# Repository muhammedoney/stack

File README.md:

# Stack — FPV uçuş kontrol ve ESC kartları

**Stack**, FPV dronlar için bir uçuş kontrol kartı (FMU) ile 4’ü 1 arada ESC kartlarından oluşan, 30.5 × 30.5 mm montaj desenli bir yığındır. Tasarımlar cezeri reposundaki Altium çalışmalarından ve piyasadaki kartların tersine mühendisliğinden geliyor; KiCad 10’a taşınacak.

```
  RC alıcı / VTX / GPS ─► [ FMU: STM32F405, ICM-42688-P, BMP388, OSD, 9 V + 5 V BEC ] ─ 8 pin SM08B ─► [ ESC: 4 × EFM8BB21 + FD6288Q + 24 MOSFET ] ─► 4 motor
                                                    ▲                                                         │
                                                    └──────────────── CUR (akım), VBAT ◄──────────────────────┘
```

## Durum (2026-11-06)

| Kart | Kaynak | Şematik | PCB | Yazılım |
|---|---|---|---|---|
| [esc55a](boards/esc55a/README.md) — 4’ü 1 arada 55 A | Altium | 3 sayfa, 232 parça | 4 katman, 41 × 48 mm, yollu (bağlanmamış 0) | BLHeli_S/Bluejay düzeni doğrulanacak |
| esc65a — 4’ü 1 arada 65 A | drawio | yok (16 fotoğraf, 2 parça etiketi) | yok | — |
| [fmu](boards/fmu/README.md) — F405 uçuş kontrol | Altium | 1 sayfa, 143 parça | yok | Betaflight hedefi yazılacak |

Altium projeleri `boards/*/altium/` altında olduğu gibi duruyor; KiCad’e taşınmadı. Bulgular ve önerilen sıra: [docs/inceleme.md](docs/inceleme.md). Gereksinimler: 5" stack için 56 SYS, 90 DOG (53 Ü-öncesi) taslak; kapı 1 onayı bekleniyor ([docs/gereksinimler](docs/gereksinimler/README.md)).

## Belgeler

| Belge | İçerik |
|---|---|
| [İlk inceleme](docs/inceleme.md) | Kopyalanan dosyalar, mimari, hesaplar, bulgular (E1–E12, F1–F7), önerilen sıra |
| [Pazar analizi](docs/pazar-analizi.md) | Rakip stack’ler, özellikler, fiyatlar, hedef değer önerisi; ham veri `docs/pazar/rakipler.csv` |
| [BOM ve maliyet](docs/bom-maliyet.md) | 5" stack 5 / 100 / 1000 set maliyeti, muadiller, maliyet azaltma seçenekleri; ham BOM `boards/*/bom-maliyet.csv` |
| [Gereksinimler](docs/gereksinimler/README.md) | MUS/SYS/PRJ/DOG kaydı, açık sorular |
| `docs/esc55a.drawio`, `docs/esc65a.drawio` | ESC tersine mühendislik çizimleri |
| `docs/fmu-diatone-f405mk2.drawio`, `docs/fmu-geprc-f405-hd-v3.drawio` | FMU referans kart çizimleri; görseller `docs/reference/fmu/` |
| [CHANGELOG](CHANGELOG.md) | Değişiklik geçmişi |

## Klasörler

| Klasör | İçerik |
|---|---|
| `boards/` | Kart başına klasör: `altium/` (orijinal), `<ad>/` (KiCad projesi, taşımadan sonra), `README.md` |
| `lib/` | Ortak KiCad kütüphanesi (taşımada kurulacak); `lib/datasheet/` veri sayfaları |
| `firmware/` | ESC (Bluejay/BLHeli_S düzeni) ve FMU (Betaflight hedefi) yazılım dosyaları |
| `docs/` | Belgeler, drawio çizimleri, `docs/gereksinimler/`, `docs/reference/` |
| `test/` | Analiz betikleri, prosedürler, DOG sonuçları |
| `tools/` | Python betikleri: `altium_sch_dump.py` (SchDoc parça/ağ dökümü), `pcb_stat.py` (içe aktarılmış PCB özeti), `drawio_dump.py` |

## Geliştirici notları

Altium dosyalarını incelemek için (repo dışına, geçici dizine):

```bash
python3 -I tools/altium_sch_dump.py boards/esc55a/altium/main.SchDoc
```

```bash
LC_ALL=C.UTF-8 kicad-cli pcb import --format altium -o /tmp/esc55a.kicad_pcb boards/esc55a/altium/ESC_v0.PcbDoc
```

**Türkçe dil ayarı:** KiCad 10.0.7’nin Altium okuyucusu alan adlarını sistem diliyle büyük harfe çeviriyor; Türkçede “Location” “LOCATİON” olur. İçe aktarmayı `LC_ALL=C.UTF-8` ile yapın.

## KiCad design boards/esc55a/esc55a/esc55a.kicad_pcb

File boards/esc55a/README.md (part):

# esc55a — 4’ü 1 arada 55 A ESC

Dört kanallı BLHeli_S tipi ESC. Kanal başına EFM8BB21F16G (QFN20) → FD6288Q (QFN24) → 6 × ME7170 N-MOS (8DFN 5 × 6). JW5026 buck → 8.07 V (PVDD) → AMS1117 → 3V3. Yüksek taraf shunt 2 × 1 mΩ 2512 + INA199C1 → J0.1 CUR. FMU bağlantısı J0 SM08B-SRSS-TB. (Altium / İP-04 durumu; **şematik Rev B’de** sürücü JSM6288Q1, MOSFET BLP016N04LC-Q 40 V, akım ölçümü 0.1 mΩ 3920 + INA240A3; yüksek sıcaklık (2026-11-11): MCU EFM8BB21F16**I** 125 °C, X5R yok — bkz. [Rev B şematik](#rev-b-şematik-2026-11-10). PCB henüz Rev A.)

- Kaynak: Altium [`altium/esc55a.PrjPcb`](altium/esc55a.PrjPcb) — `main.SchDoc` (güç, MOSFET’ler, konnektör), `mcu2.SchDoc` (kanal 1–2), `mcu.SchDoc` (kanal 3–4), `ESC_v0.PcbDoc`. `FPV_Template.PcbDoc` projede yok (eski taslak); `escPan.PcbDoc` boş 100 × 100 mm panel (cezeri 2025-05-29: “maliyet avantajı olmadı”).
- PCB: 4 katman (dış ≈ 2 oz, iç 0.5 oz), 1.67 mm, 41.25 × 47.75 mm, montaj 30.5 × 30.5 mm M3. 224 ayak izi, 1730 yol parçası, 210 via, 34 bölge; bağlanmamış 0.
- KiCad (İP-04, 2026-11-10): PCB [`esc55a/esc55a.kicad_pcb`](esc55a/esc55a.kicad_pcb) `kicad-cli pcb import` ile alındı; Altium kuralları `.kicad_pro`’da (açıklık/iz 0.1 mm, via 0.45 / 0.2 mm, halka 0.1 mm, kenar 0.2 mm); ayak izleri `lib/{RLC,MOS,IC,CONN}.pretty` (`tools/altium_libs.py`); dış hattaki 4 sıfıra yakın parça silindi (`tools/outline_fix.py`). Proje klasörü `esc55a/`: `esc55a.kicad_pcb`, `.kicad_pro` (kurallar + şematik sayfaları), `.kicad_prl`, `fp-lib-table`, `sym-lib-table`, şematik (aşağıda).

## Şematik (İP-04, 2026-11-10)

Hiyerarşik: kök [`esc55a/esc55a.kicad_sch`](esc55a/esc55a.kicad_sch) → 3 alt sayfa.

| Sayfa | Dosya | Altium kaynağı | İçerik |
|---|---|---|---|
| main (s. 2) | `main.kicad_sch` | `main.SchDoc` | Güç (JW5026, AMS1117, INA199, shunt), 24 × ME7170, J0, pedler |
| mcu2 (s. 3) | `mcu2.kicad_sch` | `mcu2.SchDoc` | Kanal 1–2: U11/U21 EFM8BB21, U12/U22 FD6288Q |
| mcu (s. 4) | `mcu.kicad_sch` | `mcu.SchDoc` | Kanal 3–4: U31/U41 EFM8BB21, U32/U42 FD6288Q |

Taşıma adımları (tekrar için):

1. `LC_ALL=C.UTF-8 LANG=C.UTF-8 kicad` → *File → Import Non-KiCad Project → Altium Project* → `altium/esc55a.PrjPcb`, hedef boş bir klasör (ör. `.tmp_imp/out/`); PCB sorusuna “No” (PCB ayrı alındı). Türkçe dil ayarında okuyucu `Location` → `LOCATİON` yapıp çöker; dil ayarı zorunlu. KiCad 10 üç sayfayı üç üst düzey sayfa olarak yazar, ağ etiketlerini yerel yapar.
2. `python3 tools/esc55a_sch.py .tmp_imp/out` — kök + alt sayfa hiyerarşisi; birden çok sayfada geçen 41 ağ etiketi global etiket (Altium projesinde port/sayfa girişi yok → etiketler global); `R?` → R99–R106, `#PWR?` numaralandı; 29 NC işareti, 16 PWR_FLAG; `.kicad_pro` sayfa listesi.
3. `python3 tools/altium_libs.py` — semboller `lib/{RLC,IC,MOS,CONN,stack}.kicad_sym`, Footprint alanları PCB’den.

| Kontrol | Sonuç |
|---|---|
| Netlist ↔ PCB (pin → ağ, 707 ortak pin) | Ağ bölünmesi/birleşmesi 0; yalnız isimsiz ağların adı farklı (`Net-(C00-1)` ↔ `NetC00_P$1`) |
| ERC (`kicad-cli sch erc`) | 0 hata, 8 uyarı: 4 sarkan 2.54 mm tel ucu (CK1–CK4 pedi, Altium artığı, elektriksel etkisi yok); 2 çoklu ağ adı (PVDD etiketi = +8V güç portu; PCB’de ağ adı PVDD); 2 sembol–kütüphane farkı (C00, C04: dikdörtgen köşe sırası, yalnız çizim) |
| Referanslar | Benzersiz. `M1aH`, `P1a`, `BAT`, `gnd`, `3v`… Altium adları PCB ile eşleşsin diye korundu (rakamla bitmediği için KiCad “annotation” uyarısı verir; **Annotate çalıştırılmamalı**) |

Şematik ↔ PCB farkları (Altium’dan gelen, değiştirilmedi):

| Konu | Şematik | PCB |
|---|---|---|
| R99–R106 (eski `R?`): kanal başına 3 k → +VD, 1 k → GND, Ux1 pin 1’e (bölücü) | Var (Rev B: DNP, kartta yok) | **Yok** (224 ayak izi); Ux1 pin 1 boşta |
| J0 `GND` pini (sembol) | Pin adı `GND`, boşta (NC) | Ayak izinde `GND` pedi yok (P1/P2 montaj pedleri ağsız) |
| R99–R106 değer adı | `RES0402_3k_????` / `RES0402_1k_????` (Altium’da da bozuk karakter) | — |

## Rev B şematik (2026-11-10)

Kaynak: [`docs/rapor/guc-ip03.md`](../../docs/rapor/guc-ip03.md) önerileri; parça kodları `bom-maliyet.csv` / `bom-revb.csv`. Betik: `python3 tools/esc55a_revb.py` (idempotent: ikinci çalıştırma dosyaları değiştirmez; yeni UUID’ler sabit adlardan). Yardımcı: `tools/sch_edit.py` (fiber’den kopya, belirlenimci UUID eklendi). **PCB değiştirilmedi** (aşağıda senkron notu).

| # | Bulgu / SYS | Değişiklik | Referanslar |
|---|---|---|---|
| 1 | G1 · SYS-014, 010 | ME7170 30 V → **BLP016N04LC-Q** 40 V 1.6 mΩ (C49328363); ALT **NTMFS5C430NLT1G** (C194661). Ayak izi aynı `MOS:8DFN4.9X5.8` (DFN5×6, 1-3 S / 4 G / 5-8 D) | M1aH…M4cL (24) |
| 2 | G3 · SYS-016 | FD6288Q → **JSM6288Q1** (C52196409, UVLO 4.5 V); ALT FD6288Q (C328453). Pin/ayak izi aynı | U12, U22, U32, U42 |
| 3 | G4 · SYS-020, 021, 013, 014 | R00 ‖ R000 (2 × 1 mΩ 2512) → **R00 0.1 mΩ 3920 10 W** (HoLRS3920, C55113241), 4 uçlu Kelvin; INA199C1 → **INA240A3DR** (×100, SOIC-8, C2060584). U2 girişleri yeni **isns_p / isns_n** ağlarında (R00 pin 2 / 3); C05 1 nF bu ikisi arasında; REF1 = REF2 = GND, pin 4 (NC) GND; çıkış filtresi R03/R04 22 Ω → curr_sens → J0.1 aynen. Yeni **C06** 100 nF U2 VS. **CUR = 10 mV/A → Betaflight `ibata_scale = 100`, `ibata_offset = 0`**; tam ölçek ≈ 310 A (3.1 V) | R00, U2, C05, C06; R000 çıktı |
| 4 | G5 · SYS-014 | SMDJ28CA → **SMDJ24CA** (DOWO C284061), SMC aynı | D00 |
| 5 | G6 · SYS-014, 083 | Bulk 29 × 22 µF 35 V X5R → **15 × 10 µF 50 V X7R 1206** (C89632). Kalan: **C1–C10, C16–C19, C48**. Çıkan (14): C26, C27, C28, C29, C30, C36, C37, C38, C39, C40, C46, C47, C50, C60. C02 4.7 µF 35 V 0603 → **4.7 µF 50 V 0805** (C98192). Set kondansatörü (≥ 470 µF, ESR ≤ 50 mΩ) kutuda zorunlu — şematik notu | C1…C60, C02 |
| 6 | G11 · SYS-016 | L00 6.8 µH 1210 → **SWPA3015S100MT** 10 µH 3 × 3 mm (C45403), yeni ayak izi | L00 |
| 7 | G12 · SYS-016 | Yeni **C07** 10 µF 16 V 0603 (C70225) +3V3 (U0 çıkışı) | C07 |
| 8 | G13 · SYS-016 | Yeni **C120/C220/C320/C420** 1 µF 25 V 0402 (C52923) her sürücü VCC (PVDD)–GND; C03 10 µF 10 V 0402 → **10 µF 16 V 0603** (C70225) | C120…C420, C03 |
| 9 | G14 · SYS-010, 070 | 24 kapı direnci 22 Ω → **10 Ω** (0402WGF100JTCE, C25077, basic). Bluejay ölü zaman ≥ 200 ns ek (`gomulu-yazilim`) | R21–R24, R26, R28 (ve R4x, R6x, R8x aynı düzen) |
| 10 | E6 / G20 · SYS-015 | R99–R106 → **DNP**, “kartta yok” (on_board = no, BOM dışı); değerler 3 k (R100, R102, R105, R106 → +VD) / 1 k (R99, R101, R103, R104 → GND); +VD ağı boşta, Ux1 P0.1 boşta | R99–R106 |
| 11 | G25 · SYS-016 | “max 15V” notu → “PVDD ≤ 12 V (U0 LDO girişi)” | not |
| 12 | SYS-091 | Tüm parçalarda Value (= sembol adı), Footprint, Datasheet (`lib/datasheet/*_<LCSC>.pdf` varsa, yoksa LCSC/TI bağlantısı), MPN, Manufacturer, LCSC; yedekli parçalarda ALT MPN / ALT Manufacturer / ALT LCSC. Altium alanları (MANUFACTURER PRODUCT NUMBER, LSCS PART NUMBER, DIGIKEY …; eski kodlar yanlıştı) silindi. Pedler ve logo BOM/dizgi dışı | hepsi |

Değişmeyenler (Rev B ilk sürüm; yüksek sıcaklıkta değişenler [aşağıda](#yüksek-sıcaklık-güncellemesi-2026-11-11)): EFM8BB21 (C80713; S1b A3 BB51 uygulanmadı — pin dizilimi farklı, onay yok), JW5026, AMS1117-3.3 (UMW), 1N4148WT, J0 (XYECONN C54582896; ALT JST C160407, ayak izi aynı varsayıldı), pasif değerler (R03/R04 22 Ω, 90.9 k, 10 k, 3.3 k, 1 k, 220 Ω). ESC ters kutup koruması yok (SOR-010, SYS-074): + / − ipek baskı PCB işi.

**Yeni semboller** (`lib/`): `MOS:NMOS 40V BLP016N04LC-Q`, `MOS:IC MOSDRV JSM6288Q1 24QFN` (kopyalar, pinler aynı); `IC:IC PWR INA240A3D SOIC-8` (INA199 kutusu, pin numaraları SOIC-8’e göre: 1 IN−, 2 GND, 3 REF2, 4 NC, 5 OUT, 6 VS, 7 REF1, 8 IN+ — TI SBOS662 Tablo 6-1); `RLC:RES3920_0m1_KELVIN` (KiCad `Device:R_Shunt`: 1/4 güç, 2/3 algılama); `RLC:` DTVS_SMDJ24CA, IND3015_10u, CAP1206_10u_50V_X7R, CAP0805_4u7_50V_X5R, CAP0603_10u_16V_X5R, CAP0402_1u_25V_X5R, RES0402_10, RES0402_3k. CAP0402_0u1_16V/50V_X7R kütüphane kopyası şematikle eşitlendi (yalnız çizim).
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
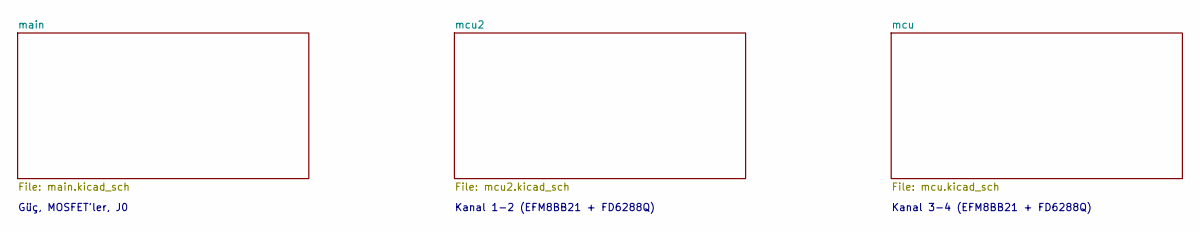
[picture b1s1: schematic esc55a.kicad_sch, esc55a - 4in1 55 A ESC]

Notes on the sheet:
Güç, MOSFET'ler, J0
Kanal 1-2 (EFM8BB21 + FD6288Q)
Kanal 3-4 (EFM8BB21 + FD6288Q)

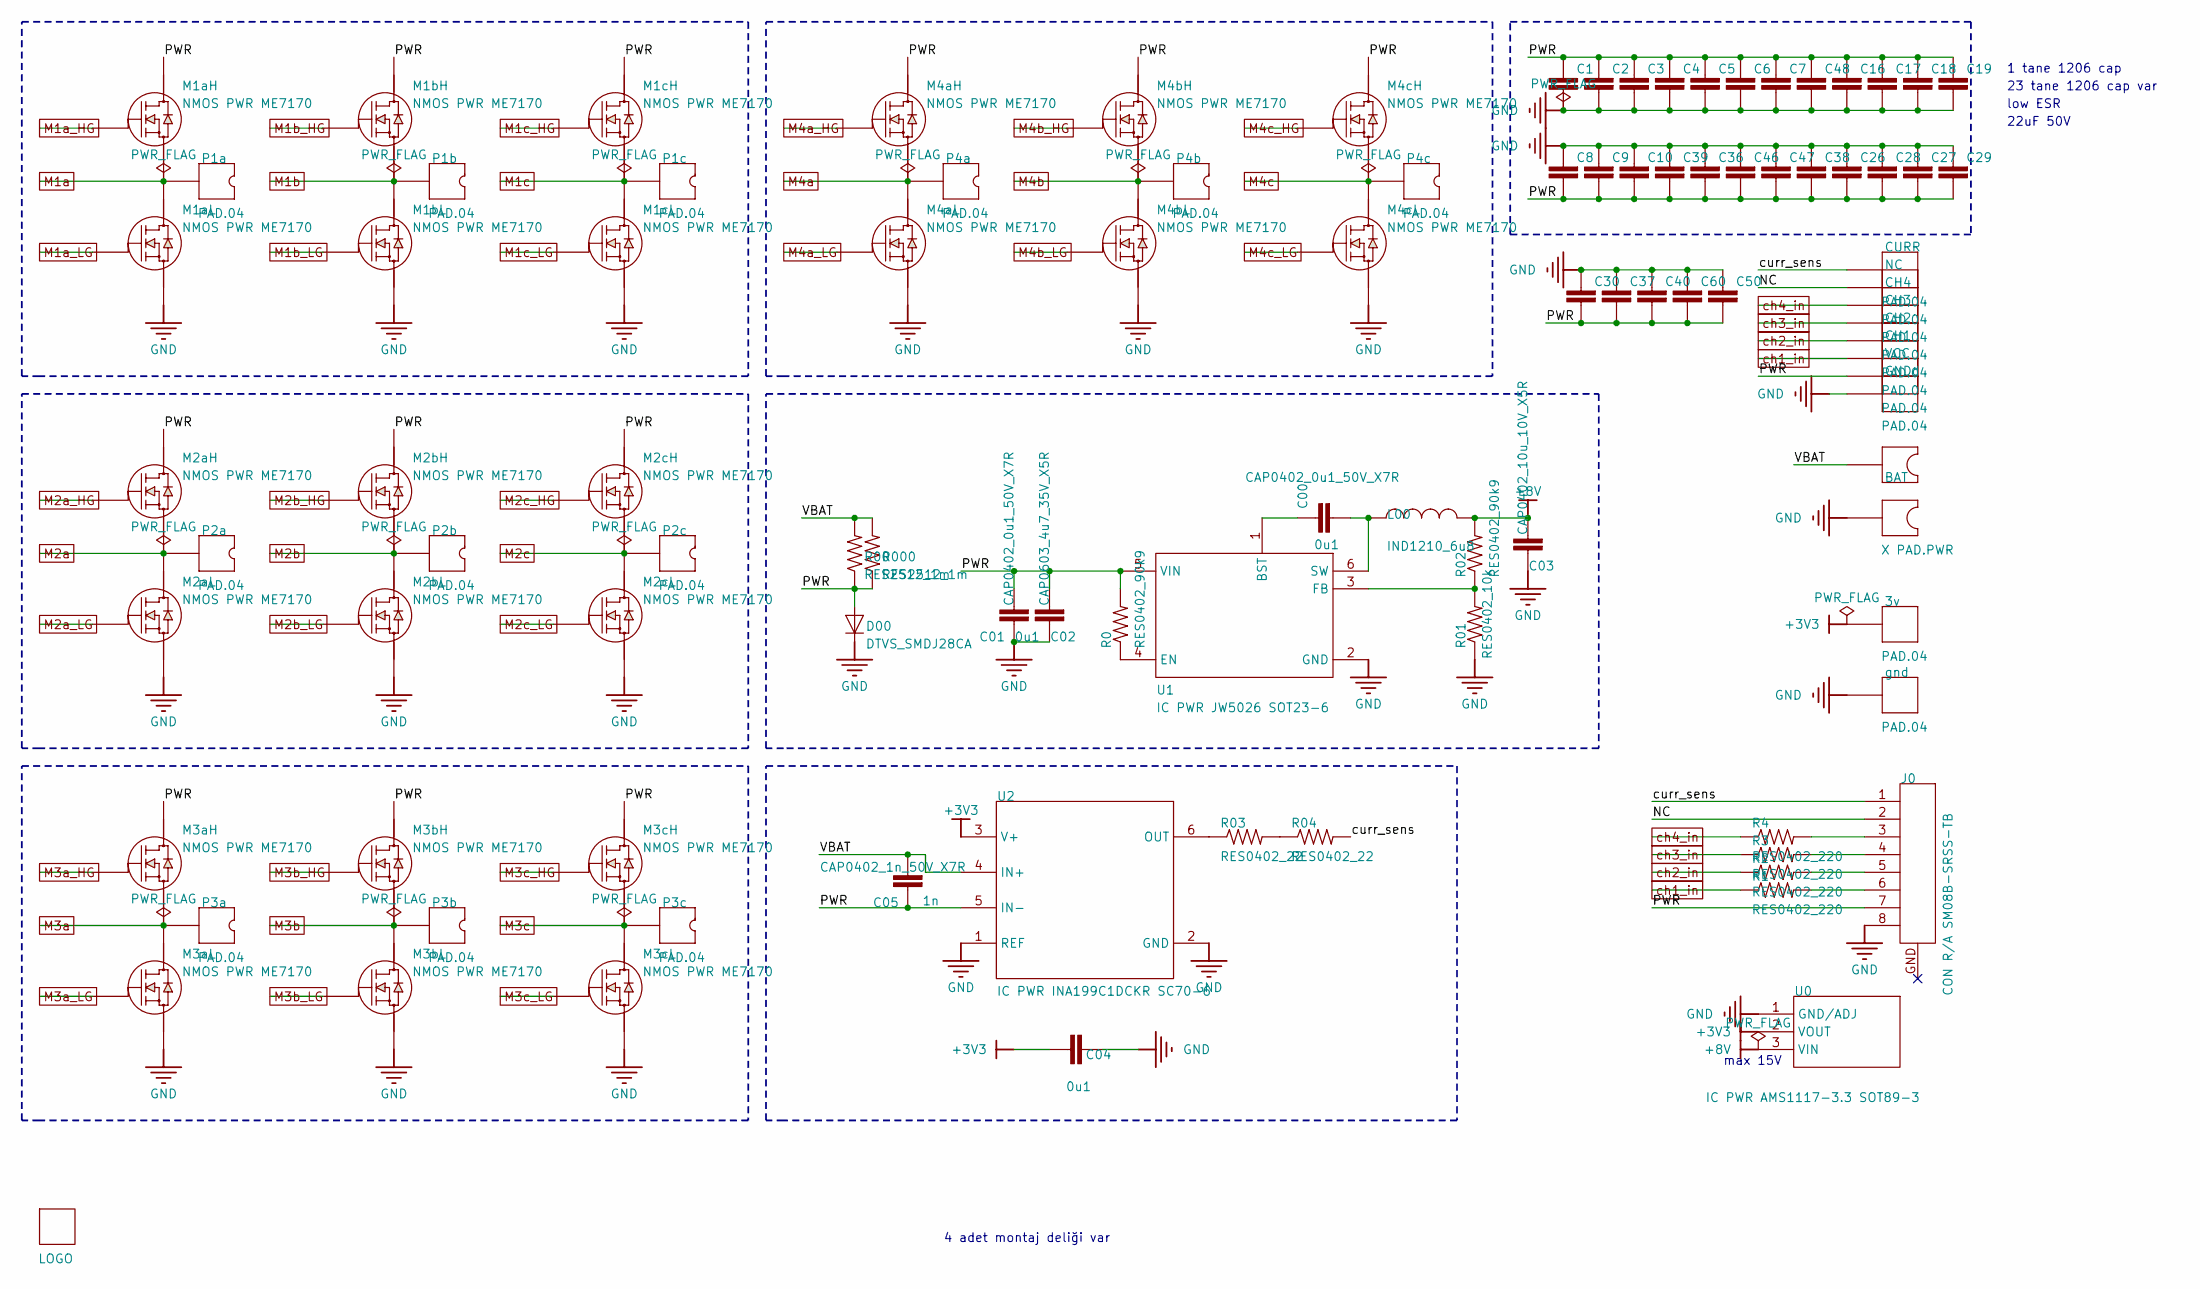
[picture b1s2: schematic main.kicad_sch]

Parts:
3v: PAD.04; PAD.04X.04
BAT: X PAD.PWR; PAD6x8
C00, C01: CAP0402_0u1_50V_X7R; 0402-CAP; VOLTAGE RATING 50; DIGIKEY PART NUMBER 490-10700-1-ND
C1, C2, C3, C4, C5, C6, C7, C8, C9, C10, C16, C17, C18, C19, C26, C27, C28, C29, C30, C36, C37, C38, C39, C40, C46, C47, C48, C50, C60: CAP1206_22u_35V_X5R; 1206-CAP; VOLTAGE RATING 35; DIGIKEY PART NUMBER 445-8045-1-ND
C02: CAP0603_4u7_35V_X5R; 0603-CAP; VOLTAGE RATING 35V; DIGIKEY PART NUMBER 490-7205-1-ND
C03: CAP0402_10u_10V_X5R; 0402-CAP; VOLTAGE RATING 10V; DIGIKEY PART NUMBER N/A
C04: CAP0402_0u1_16V_X7R; 0402-CAP; VOLTAGE RATING 16; DIGIKEY PART NUMBER 1276-1507-1-ND
C05: CAP0402_1n_50V_X7R; 0402-CAP; VOLTAGE RATING 50; DIGIKEY PART NUMBER 311-1036-1-ND
CH1, CH2, CH3, CH4: PAD.04; PAD.04X.04
CURR: PAD.04; PAD.04X.04
D00: DTVS_SMDJ28CA; SMC-TVS; DIGIKEY PART NUMBER SMDJ28CACT-ND
GNDd: PAD.04; PAD.04X.04
J0: CON R/A SM08B-SRSS-TB; JST_SM08B-SRSS-TB; DIGIKEY PART NUMBER 455-1808-1-ND
L00: IND1210_6u8; 1210-IND; DIGIKEY PART NUMBER 445-TFM322512ALMA6R8MTAACT-ND
LOGO: 00 LOGO FTECH; 00FTECH
M1aH, M1aL, M1bH, M1bL, M1cH, M1cL, M2aH, M2aL, M2bH, M2bL, M2cH, M2cL, M3aH, M3aL, M3bH, M3bL, M3cH, M3cL, M4aH, M4aL, M4bH, M4bL, M4cH, M4cL: NMOS PWR ME7170; 8DFN4.9X5.8; DIGIKEY PART NUMBER N/A
NC: PAD.04; PAD.04X.04
P1a, P1b, P1c, P2a, P2b, P2c, P3a, P3b, P3c, P4a, P4b, P4c: PAD.04; PAD3.2x3.2
R0, R02: RES0402_90k9; 0402-RES; DIGIKEY PART NUMBER 311-90.9KLRCT-ND
R00, R000: RES2512_1m; 2512-RES; DIGIKEY PART NUMBER YAG6089CT-ND
R01: RES0402_10k; 0402-RES; DIGIKEY PART NUMBER 311-10.0KLRCT-ND
R1, R2, R3, R4: RES0402_220; 0402-RES; DIGIKEY PART NUMBER 311-220LRCT-ND
R03, R04: RES0402_22; 0402-RES; DIGIKEY PART NUMBER 311-22.0LRCT-ND
U0: IC PWR AMS1117-3.3 SOT89-3; SOT89-3; VOLTAGE RATING 15V; OUTPUT VOLTAGE 3.3V; DIGIKEY PART NUMBER 5272-AMS1117-3.3SCT-ND
U1: IC PWR JW5026 SOT23-6; SOT23-6; DIGIKEY PART NUMBER N/A
U2: IC PWR INA199C1DCKR SC70-6; SC70-6; DIGIKEY PART NUMBER 296-47775-1-ND
VCC: PAD.04; PAD.04X.04
gnd: PAD.04; PAD.04X.04

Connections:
+3V3: 3v.P$1, C04.P$1 (1), U0.2 (VOUT), U2.3 (V+); also elsewhere on the board
GND: BAT.P$2, C01.P$2 (2), C1.P$2 (2), C02.P$2 (2), C2.P$2 (2), C03.P$2 (2), C3.P$2 (2), C04.P$2 (2), C4.P$2 (2), C5.P$2 (2), C6.P$2 (2), C7.P$2 (2), C8.P$1 (1), C9.P$1 (1), C10.P$1 (1), C16.P$2 (2), C17.P$2 (2), C18.P$2 (2), C19.P$2 (2), C26.P$1 (1), C27.P$1 (1), C28.P$1 (1), C29.P$1 (1), C30.P$1 (1), C36.P$1 (1), C37.P$1 (1), C38.P$1 (1), C39.P$1 (1), C40.P$1 (1), C46.P$1 (1), C47.P$1 (1), C48.P$2 (2), C50.P$1 (1), C60.P$1 (1), D00.C, GNDd.P$1, J0.8, M1aL.1, M1aL.2, M1aL.3, M1bL.1, M1bL.2, M1bL.3, M1cL.1, M1cL.2, M1cL.3, M2aL.1, M2aL.2, M2aL.3, M2bL.1, M2bL.2, M2bL.3, M2cL.1, M2cL.2, M2cL.3, M3aL.1, M3aL.2, M3aL.3, M3bL.1, M3bL.2, M3bL.3, M3cL.1, M3cL.2, M3cL.3, M4aL.1, M4aL.2, M4aL.3, M4bL.1, M4bL.2, M4bL.3, M4cL.1, M4cL.2, M4cL.3, R01.P$1 (1), U0.1 (GND/ADJ), U1.2 (GND), U2.1 (REF), U2.2 (GND), gnd.P$1; also elsewhere on the board
M1a: M1aH.1, M1aH.2, M1aH.3, M1aL.5, M1aL.6, M1aL.7, M1aL.8, P1a.P$1; also elsewhere on the board
M1a_HG: M1aH.4; also elsewhere on the board
M1a_LG: M1aL.4; also elsewhere on the board
M1b: M1bH.1, M1bH.2, M1bH.3, M1bL.5, M1bL.6, M1bL.7, M1bL.8, P1b.P$1; also elsewhere on the board
M1b_HG: M1bH.4; also elsewhere on the board
M1b_LG: M1bL.4; also elsewhere on the board
M1c: M1cH.1, M1cH.2, M1cH.3, M1cL.5, M1cL.6, M1cL.7, M1cL.8, P1c.P$1; also elsewhere on the board
M1c_HG: M1cH.4; also elsewhere on the board
M1c_LG: M1cL.4; also elsewhere on the board
M2a: M2aH.1, M2aH.2, M2aH.3, M2aL.5, M2aL.6, M2aL.7, M2aL.8, P2a.P$1; also elsewhere on the board
M2a_HG: M2aH.4; also elsewhere on the board
M2a_LG: M2aL.4; also elsewhere on the board
M2b: M2bH.1, M2bH.2, M2bH.3, M2bL.5, M2bL.6, M2bL.7, M2bL.8, P2b.P$1; also elsewhere on the board
M2b_HG: M2bH.4; also elsewhere on the board
M2b_LG: M2bL.4; also elsewhere on the board
M2c: M2cH.1, M2cH.2, M2cH.3, M2cL.5, M2cL.6, M2cL.7, M2cL.8, P2c.P$1; also elsewhere on the board
M2c_HG: M2cH.4; also elsewhere on the board
M2c_LG: M2cL.4; also elsewhere on the board
M3a: M3aH.1, M3aH.2, M3aH.3, M3aL.5, M3aL.6, M3aL.7, M3aL.8, P3a.P$1; also elsewhere on the board
M3a_HG: M3aH.4; also elsewhere on the board
M3a_LG: M3aL.4; also elsewhere on the board
M3b: M3bH.1, M3bH.2, M3bH.3, M3bL.5, M3bL.6, M3bL.7, M3bL.8, P3b.P$1; also elsewhere on the board
M3b_HG: M3bH.4; also elsewhere on the board
M3b_LG: M3bL.4; also elsewhere on the board
M3c: M3cH.1, M3cH.2, M3cH.3, M3cL.5, M3cL.6, M3cL.7, M3cL.8, P3c.P$1; also elsewhere on the board
M3c_HG: M3cH.4; also elsewhere on the board
M3c_LG: M3cL.4; also elsewhere on the board
M4a: M4aH.1, M4aH.2, M4aH.3, M4aL.5, M4aL.6, M4aL.7, M4aL.8, P4a.P$1; also elsewhere on the board
M4a_HG: M4aH.4; also elsewhere on the board
M4a_LG: M4aL.4; also elsewhere on the board
M4b: M4bH.1, M4bH.2, M4bH.3, M4bL.5, M4bL.6, M4bL.7, M4bL.8, P4b.P$1; also elsewhere on the board
M4b_HG: M4bH.4; also elsewhere on the board
M4b_LG: M4bL.4; also elsewhere on the board
M4c: M4cH.1, M4cH.2, M4cH.3, M4cL.5, M4cL.6, M4cL.7, M4cL.8, P4c.P$1; also elsewhere on the board
M4c_HG: M4cH.4; also elsewhere on the board
M4c_LG: M4cL.4; also elsewhere on the board
NC: J0.2, NC.P$1
NetC00_P$1: C00.P$1 (1), L00.1, U1.6 (SW)
NetC00_P$2: C00.P$2 (2), U1.1 (BST)
NetJ0_3: J0.3, R4.P$2 (2)
NetJ0_4: J0.4, R3.P$2 (2)
NetJ0_5: J0.5, R2.P$2 (2)
NetJ0_6: J0.6, R1.P$2 (2)
NetR0_P$1: R0.P$1 (1), U1.4 (EN)
NetR01_P$2: R01.P$2 (2), R02.P$1 (1), U1.3 (FB)
NetR03_P$1: R03.P$1 (1), U2.6 (OUT)
NetR03_P$2: R03.P$2 (2), R04.P$1 (1)
PVDD: C03.P$1 (1), L00.2, R02.P$2 (2), U0.3 (VIN); also elsewhere on the board
PWR: C01.P$1 (1), C1.P$1 (1), C02.P$1 (1), C2.P$1 (1), C3.P$1 (1), C4.P$1 (1), C5.P$1 (1), C05.P$2 (2), C6.P$1 (1), C7.P$1 (1), C8.P$2 (2), C9.P$2 (2), C10.P$2 (2), C16.P$1 (1), C17.P$1 (1), C18.P$1 (1), C19.P$1 (1), C26.P$2 (2), C27.P$2 (2), C28.P$2 (2), C29.P$2 (2), C30.P$2 (2), C36.P$2 (2), C37.P$2 (2), C38.P$2 (2), C39.P$2 (2), C40.P$2 (2), C46.P$2 (2), C47.P$2 (2), C48.P$1 (1), C50.P$2 (2), C60.P$2 (2), D00.A, J0.7, M1aH.5, M1aH.6, M1aH.7, M1aH.8, M1bH.5, M1bH.6, M1bH.7, M1bH.8, M1cH.5, M1cH.6, M1cH.7, M1cH.8, M2aH.5, M2aH.6, M2aH.7, M2aH.8, M2bH.5, M2bH.6, M2bH.7, M2bH.8, M2cH.5, M2cH.6, M2cH.7, M2cH.8, M3aH.5, M3aH.6, M3aH.7, M3aH.8, M3bH.5, M3bH.6, M3bH.7, M3bH.8, M3cH.5, M3cH.6, M3cH.7, M3cH.8, M4aH.5, M4aH.6, M4aH.7, M4aH.8, M4bH.5, M4bH.6, M4bH.7, M4bH.8, M4cH.5, M4cH.6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
VBAT: BAT.P$1, C05.P$1 (1), R00.P$2 (2), R000.P$2 (2), U2.4 (IN+)
ch1_in: CH1.P$1, R1.P$1 (1); also elsewhere on the board
ch2_in: CH2.P$1, R2.P$1 (1); also elsewhere on the board
ch3_in: CH3.P$1, R3.P$1 (1); also elsewhere on the board
ch4_in: CH4.P$1, R4.P$1 (1); also elsewhere on the board
curr_sens: CURR.P$1, J0.1, R04.P$2 (2)

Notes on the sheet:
23 tane 1206 cap var
4 adet montaj deliği var
22uF 50V
max 15V
1 tane 1206 cap
low ESR

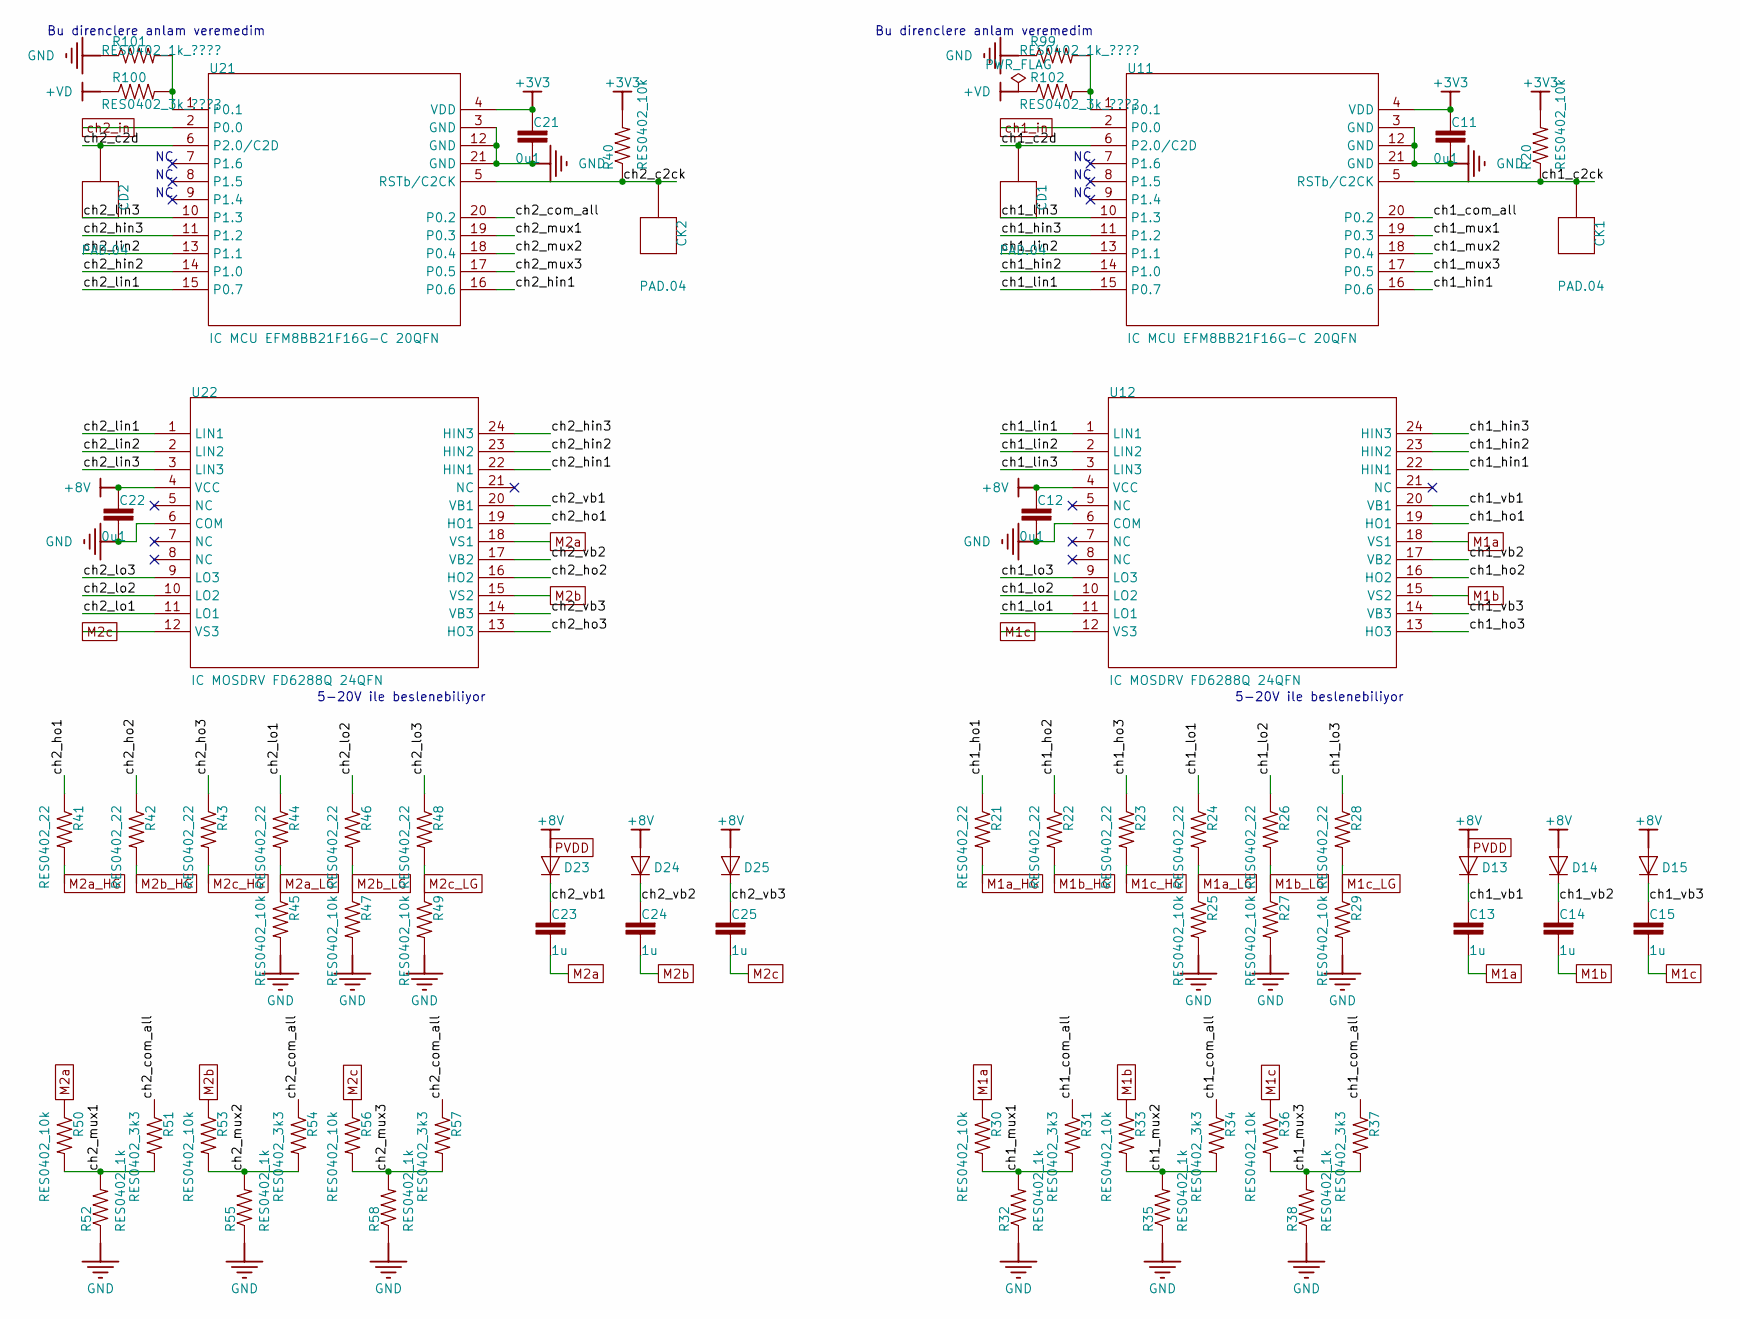
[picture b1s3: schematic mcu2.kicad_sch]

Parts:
C11, C12, C21, C22: CAP0402_0u1_16V_X7R; 0402-CAP; VOLTAGE RATING 16; DIGIKEY PART NUMBER 1276-1507-1-ND
C13, C14, C15, C23, C24, C25: CAP0402_1u_16V_X5R; 0402-CAP; VOLTAGE RATING 16V; DIGIKEY PART NUMBER 1276-1067-1-ND
CD1, CD2: PAD.04; PAD.04X.04
CK1, CK2: PAD.04; PAD.04X.04
D13, D14, D15, D23, D24, D25: DPWR_1N4148WT; SOD-523_0P9X1P3; DIGIKEY PART NUMBER 1N4148WTCT-ND
R20, R25, R27, R29, R30, R33, R36, R40, R45, R47, R49, R50, R53, R56: RES0402_10k; 0402-RES; DIGIKEY PART NUMBER 311-10.0KLRCT-ND
R21, R22, R23, R24, R26, R28, R41, R42, R43, R44, R46, R48: RES0402_22; 0402-RES; DIGIKEY PART NUMBER 311-22.0LRCT-ND
R31, R34, R37, R51, R54, R57: RES0402_3k3; 0402-RES; DIGIKEY PART NUMBER 1712-CRG0402F3K3CT-ND
R32, R35, R38, R52, R55, R58: RES0402_1k; 0402-RES; DIGIKEY PART NUMBER 311-1.0KJRCT-ND
R99, R101: RES0402_1k_????; 0402-RES
R100, R102: RES0402_3k_????; 0402-RES
U11, U21: IC MCU EFM8BB21F16G-C 20QFN; QFN20_3X3_SIL; DIGIKEY PART NUMBER 336-4743-1-ND
U12, U22: IC MOSDRV FD6288Q 24QFN; QFN-24(4x4); DIGIKEY PART NUMBER N/A

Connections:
+3V3: C11.P$1 (1), C21.P$1 (1), R20.P$2 (2), R40.P$2 (2), U11.4 (VDD), U21.4 (VDD); also elsewhere on the board
GND: C11.P$2 (2), C12.P$2 (2), C21.P$2 (2), C22.P$2 (2), R25.P$2 (2), R27.P$2 (2), R29.P$2 (2), R32.P$1 (1), R35.P$1 (1), R38.P$1 (1), R45.P$2 (2), R47.P$2 (2), R49.P$2 (2), R52.P$1 (1), R55.P$1 (1), R58.P$1 (1), R99.P$1 (1), R101.P$1 (1), U11.3 (GND), U11.12 (GND), U11.21 (GND), U12.6 (COM), U21.3 (GND), U21.12 (GND), U21.21 (GND), U22.6 (COM); also elsewhere on the board
M1a: C13.P$2 (2), R30.P$1 (1), U12.18 (VS1); also elsewhere on the board
M1a_HG: R21.P$2 (2); also elsewhere on the board
M1a_LG: R24.P$2 (2), R25.P$1 (1); also elsewhere on the board
M1b: C14.P$2 (2), R33.P$1 (1), U12.15 (VS2); also elsewhere on the board
M1b_HG: R22.P$2 (2); also elsewhere on the board
M1b_LG: R26.P$2 (2), R27.P$1 (1); also elsewhere on the board
M1c: C15.P$2 (2), R36.P$1 (1), U12.12 (VS3); also elsewhere on the board
M1c_HG: R23.P$2 (2); also elsewhere on the board
M1c_LG: R28.P$2 (2), R29.P$1 (1); also elsewhere on the board
M2a: C23.P$2 (2), R50.P$1 (1), U22.18 (VS1); also elsewhere on the board
M2a_HG: R41.P$2 (2); also elsewhere on the board
M2a_LG: R44.P$2 (2), R45.P$1 (1); also elsewhere on the board
M2b: C24.P$2 (2), R53.P$1 (1), U22.15 (VS2); also elsewhere on the board
M2b_HG: R42.P$2 (2); also elsewhere on the board
M2b_LG: R46.P$2 (2), R47.P$1 (1); also elsewhere on the board
M2c: C25.P$2 (2), R56.P$1 (1), U22.12 (VS3); also elsewhere on the board
M2c_HG: R43.P$2 (2); also elsewhere on the board
M2c_LG: R48.P$2 (2), R49.P$1 (1); also elsewhere on the board
unnamed: R100.P$1 (1), R102.P$1 (1)
unnamed: R100.P$2 (2), R101.P$2 (2), U21.1 (P0.1)
unnamed: R99.P$2 (2), R102.P$2 (2), U11.1 (P0.1)
PVDD: C12.P$1 (1), C22.P$1 (1), D13.A, D14.A, D15.A, D23.A, D24.A, D25.A, U12.4 (VCC), U22.4 (VCC); also elsewhere on the board
ch1_c2ck: CK1.P$1, R20.P$1 (1), U11.5 (RSTb/C2CK)
ch1_c2d: CD1.P$1, U11.6 (P2.0/C2D)
ch1_com_all: R31.P$1 (1), R34.P$1 (1), R37.P$1 (1), U11.20 (P0.2)
ch1_hin1: U11.16 (P0.6), U12.22 (HIN1)
ch1_hin2: U11.14 (P1.0), U12.23 (HIN2)
ch1_hin3: U11.11 (P1.2), U12.24 (HIN3)
ch1_ho1: R21.P$1 (1), U12.19 (HO1)
ch1_ho2: R22.P$1 (1), U12.16 (HO2)
ch1_ho3: R23.P$1 (1), U12.13 (HO3)
ch1_in: U11.2 (P0.0); also elsewhere on the board
ch1_lin1: U11.15 (P0.7), U12.1 (LIN1)
ch1_lin2: U11.13 (P1.1), U12.2 (LIN2)
ch1_lin3: U11.10 (P1.3), U12.3 (LIN3)
ch1_lo1: R24.P$1 (1), U12.11 (LO1)
ch1_lo2: R26.P$1 (1), U12.10 (LO2)
ch1_lo3: R28.P$1 (1), U12.9 (LO3)
ch1_mux1: R30.P$2 (2), R31.P$2 (2), R32.P$2 (2), U11.19 (P0.3)
ch1_mux2: R33.P$2 (2), R34.P$2 (2), R35.P$2 (2), U11.18 (P0.4)
ch1_mux3: R36.P$2 (2), R37.P$2 (2), R38.P$2 (2), U11.17 (P0.5)
ch1_vb1: C13.P$1 (1), D13.K, U12.20 (VB1)
ch1_vb2: C14.P$1 (1), D14.K, U12.17 (VB2)
ch1_vb3: C15.P$1 (1), D15.K, U12.14 (VB3)
ch2_c2ck: CK2.P$1, R40.P$1 (1), U21.5 (RSTb/C2CK)
ch2_c2d: CD2.P$1, U21.6 (P2.0/C2D)
ch2_com_all: R51.P$1 (1), R54.P$1 (1), R57.P$1 (1), U21.20 (P0.2)
ch2_hin1: U21.16 (P0.6), U22.22 (HIN1)
ch2_hin2: U21.14 (P1.0), U22.23 (HIN2)
ch2_hin3: U21.11 (P1.2), U22.24 (HIN3)
ch2_ho1: R41.P$1 (1), U22.19 (HO1)
ch2_ho2: R42.P$1 (1), U22.16 (HO2)
ch2_ho3: R43.P$1 (1), U22.13 (HO3)
ch2_in: U21.2 (P0.0); also elsewhere on the board
ch2_lin1: U21.15 (P0.7), U22.1 (LIN1)
ch2_lin2: U21.13 (P1.1), U22.2 (LIN2)
ch2_lin3: U21.10 (P1.3), U22.3 (LIN3)
ch2_lo1: R44.P$1 (1), U22.11 (LO1)
ch2_lo2: R46.P$1 (1), U22.10 (LO2)
ch2_lo3: R48.P$1 (1), U22.9 (LO3)
ch2_mux1: R50.P$2 (2), R51.P$2 (2), R52.P$2 (2), U21.19 (P0.3)
ch2_mux2: R53.P$2 (2), R54.P$2 (2), R55.P$2 (2), U21.18 (P0.4)
ch2_mux3: R56.P$2 (2), R57.P$2 (2), R58.P$2 (2), U21.17 (P0.5)
ch2_vb1: C23.P$1 (1), D23.K, U22.20 (VB1)
ch2_vb2: C24.P$1 (1), D24.K, U22.17 (VB2)
ch2_vb3: C25.P$1 (1), D25.K, U22.14 (VB3)

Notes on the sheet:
Bu direnclere anlam veremedim
5-20V ile beslenebiliyor

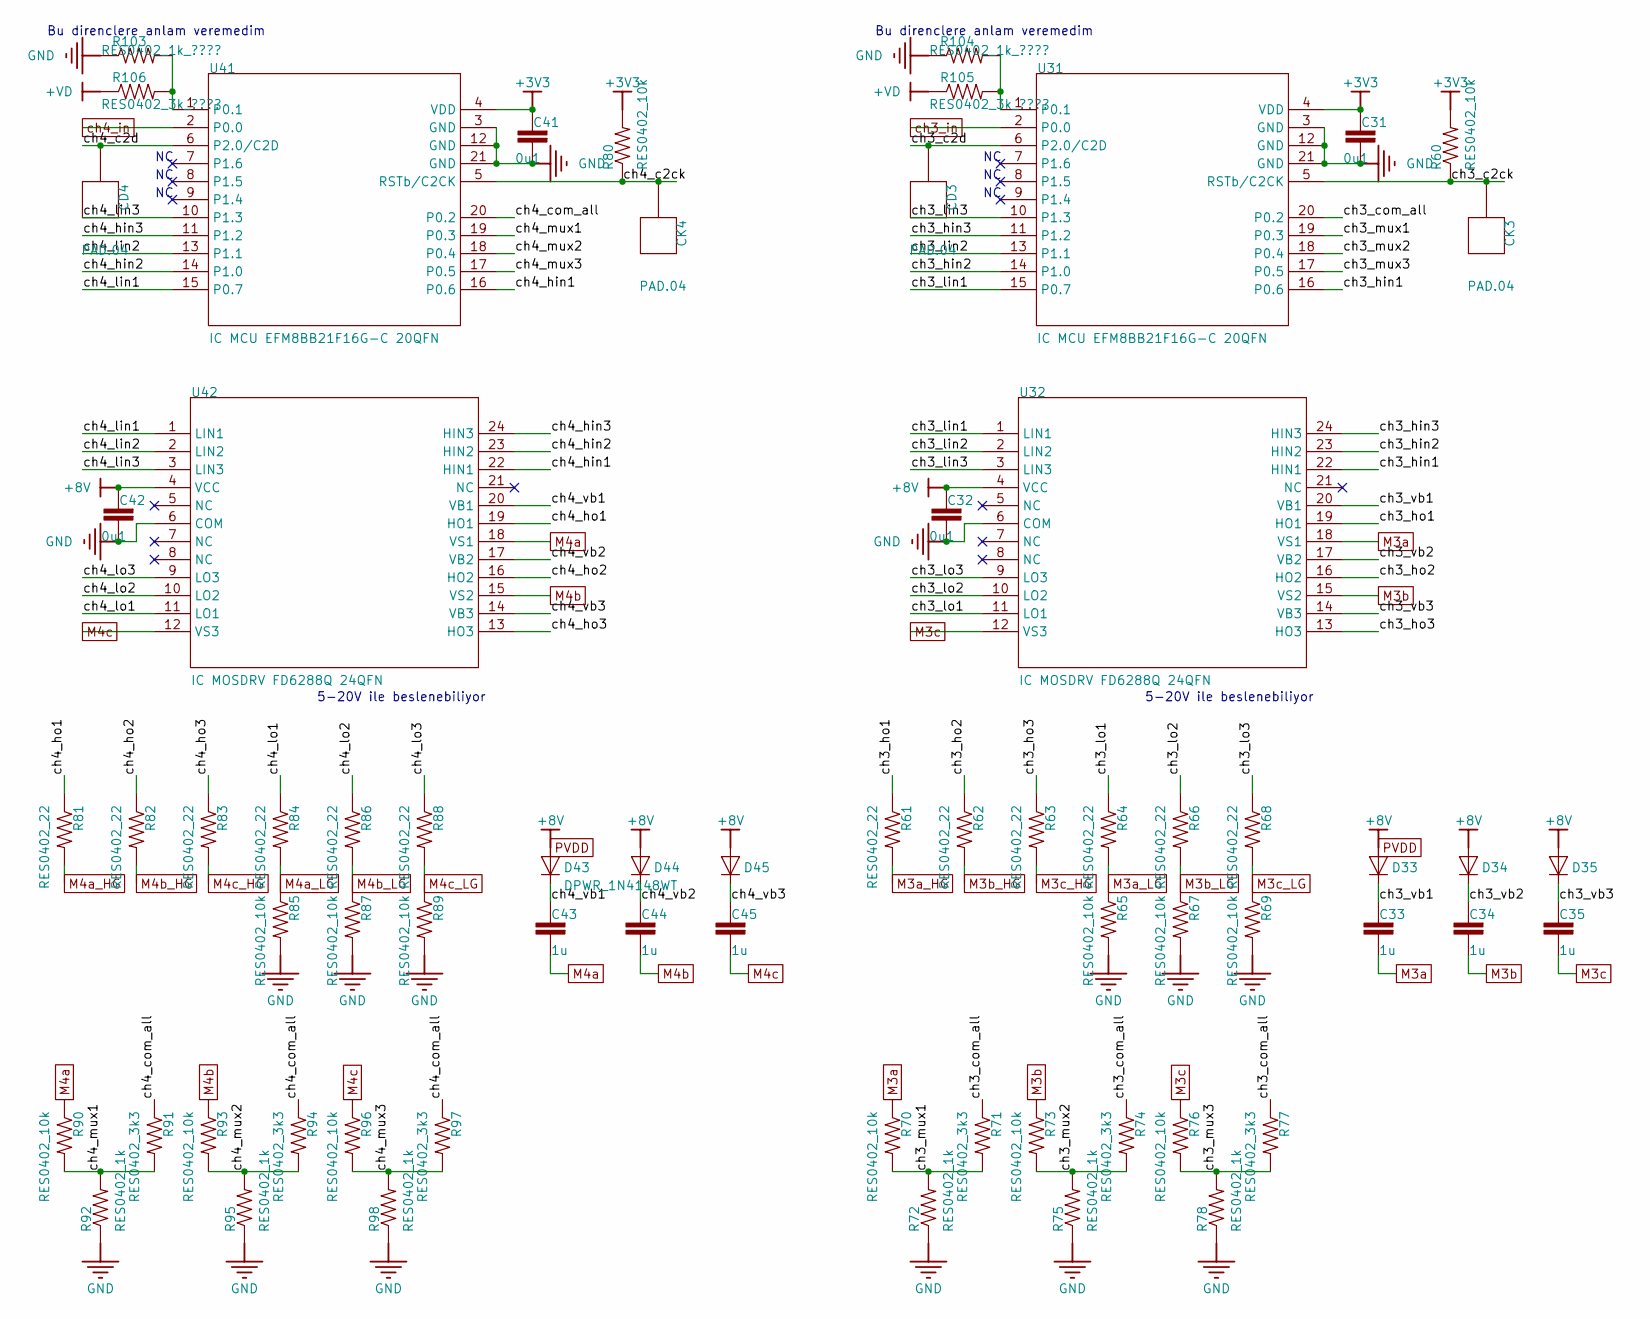
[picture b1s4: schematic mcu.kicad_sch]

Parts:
C31, C32, C41, C42: CAP0402_0u1_16V_X7R; 0402-CAP; VOLTAGE RATING 16; DIGIKEY PART NUMBER 1276-1507-1-ND
C33, C34, C35, C43, C44, C45: CAP0402_1u_16V_X5R; 0402-CAP; VOLTAGE RATING 16V; DIGIKEY PART NUMBER 1276-1067-1-ND
CD3, CD4: PAD.04; PAD.04X.04
CK3, CK4: PAD.04; PAD.04X.04
D33, D34, D35, D43, D44, D45: DPWR_1N4148WT; SOD-523_0P9X1P3; DIGIKEY PART NUMBER 1N4148WTCT-ND
R60, R65, R67, R69, R70, R73, R76, R80, R85, R87, R89, R90, R93, R96: RES0402_10k; 0402-RES; DIGIKEY PART NUMBER 311-10.0KLRCT-ND
R61, R62, R63, R64, R66, R68, R81, R82, R83, R84, R86, R88: RES0402_22; 0402-RES; DIGIKEY PART NUMBER 311-22.0LRCT-ND
R71, R74, R77, R91, R94, R97: RES0402_3k3; 0402-RES; DIGIKEY PART NUMBER 1712-CRG0402F3K3CT-ND
R72, R75, R78, R92, R95, R98: RES0402_1k; 0402-RES; DIGIKEY PART NUMBER 311-1.0KJRCT-ND
R103, R104: RES0402_1k_????; 0402-RES
R105, R106: RES0402_3k_????; 0402-RES
U31, U41: IC MCU EFM8BB21F16G-C 20QFN; QFN20_3X3_SIL; DIGIKEY PART NUMBER 336-4743-1-ND
U32, U42: IC MOSDRV FD6288Q 24QFN; QFN-24(4x4); DIGIKEY PART NUMBER N/A

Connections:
+3V3: C31.P$1 (1), C41.P$1 (1), R60.P$2 (2), R80.P$2 (2), U31.4 (VDD), U41.4 (VDD); also elsewhere on the board
GND: C31.P$2 (2), C32.P$2 (2), C41.P$2 (2), C42.P$2 (2), R65.P$2 (2), R67.P$2 (2), R69.P$2 (2), R72.P$1 (1), R75.P$1 (1), R78.P$1 (1), R85.P$2 (2), R87.P$2 (2), R89.P$2 (2), R92.P$1 (1), R95.P$1 (1), R98.P$1 (1), R103.P$1 (1), R104.P$1 (1), U31.3 (GND), U31.12 (GND), U31.21 (GND), U32.6 (COM), U41.3 (GND), U41.12 (GND), U41.21 (GND), U42.6 (COM); also elsewhere on the board
M3a: C33.P$2 (2), R70.P$1 (1), U32.18 (VS1); also elsewhere on the board
M3a_HG: R61.P$2 (2); also elsewhere on the board
M3a_LG: R64.P$2 (2), R65.P$1 (1); also elsewhere on the board
M3b: C34.P$2 (2), R73.P$1 (1), U32.15 (VS2); also elsewhere on the board
M3b_HG: R62.P$2 (2); also elsewhere on the board
M3b_LG: R66.P$2 (2), R67.P$1 (1); also elsewhere on the board
M3c: C35.P$2 (2), R76.P$1 (1), U32.12 (VS3); also elsewhere on the board
M3c_HG: R63.P$2 (2); also elsewhere on the board
M3c_LG: R68.P$2 (2), R69.P$1 (1); also elsewhere on the board
M4a: C43.P$2 (2), R90.P$1 (1), U42.18 (VS1); also elsewhere on the board
M4a_HG: R81.P$2 (2); also elsewhere on the board
M4a_LG: R84.P$2 (2), R85.P$1 (1); also elsewhere on the board
M4b: C44.P$2 (2), R93.P$1 (1), U42.15 (VS2); also elsewhere on the board
M4b_HG: R82.P$2 (2); also elsewhere on the board
M4b_LG: R86.P$2 (2), R87.P$1 (1); also elsewhere on the board
M4c: C45.P$2 (2), R96.P$1 (1), U42.12 (VS3); also elsewhere on the board
M4c_HG: R83.P$2 (2); also elsewhere on the board
M4c_LG: R88.P$2 (2), R89.P$1 (1); also elsewhere on the board
unnamed: R103.P$2 (2), R106.P$2 (2), U41.1 (P0.1)
unnamed: R104.P$2 (2), R105.P$2 (2), U31.1 (P0.1)
unnamed: R105.P$1 (1), R106.P$1 (1)
PVDD: C32.P$1 (1), C42.P$1 (1), D33.A, D34.A, D35.A, D43.A, D44.A, D45.A, U32.4 (VCC), U42.4 (VCC); also elsewhere on the board
ch3_c2ck: CK3.P$1, R60.P$1 (1), U31.5 (RSTb/C2CK)
ch3_c2d: CD3.P$1, U31.6 (P2.0/C2D)
ch3_com_all: R71.P$1 (1), R74.P$1 (1), R77.P$1 (1), U31.20 (P0.2)
ch3_hin1: U31.16 (P0.6), U32.22 (HIN1)
ch3_hin2: U31.14 (P1.0), U32.23 (HIN2)
ch3_hin3: U31.11 (P1.2), U32.24 (HIN3)
ch3_ho1: R61.P$1 (1), U32.19 (HO1)
ch3_ho2: R62.P$1 (1), U32.16 (HO2)
ch3_ho3: R63.P$1 (1), U32.13 (HO3)
ch3_in: U31.2 (P0.0); also elsewhere on the board
ch3_lin1: U31.15 (P0.7), U32.1 (LIN1)
ch3_lin2: U31.13 (P1.1), U32.2 (LIN2)
ch3_lin3: U31.10 (P1.3), U32.3 (LIN3)
ch3_lo1: R64.P$1 (1), U32.11 (LO1)
ch3_lo2: R66.P$1 (1), U32.10 (LO2)
ch3_lo3: R68.P$1 (1), U32.9 (LO3)
ch3_mux1: R70.P$2 (2), R71.P$2 (2), R72.P$2 (2), U31.19 (P0.3)
ch3_mux2: R73.P$2 (2), R74.P$2 (2), R75.P$2 (2), U31.18 (P0.4)
ch3_mux3: R76.P$2 (2), R77.P$2 (2), R78.P$2 (2), U31.17 (P0.5)
ch3_vb1: C33.P$1 (1), D33.K, U32.20 (VB1)
ch3_vb2: C34.P$1 (1), D34.K, U32.17 (VB2)
ch3_vb3: C35.P$1 (1), D35.K, U32.14 (VB3)
ch4_c2ck: CK4.P$1, R80.P$1 (1), U41.5 (RSTb/C2CK)
ch4_c2d: CD4.P$1, U41.6 (P2.0/C2D)
ch4_com_all: R91.P$1 (1), R94.P$1 (1), R97.P$1 (1), U41.20 (P0.2)
ch4_hin1: U41.16 (P0.6), U42.22 (HIN1)
ch4_hin2: U41.14 (P1.0), U42.23 (HIN2)
ch4_hin3: U41.11 (P1.2), U42.24 (HIN3)
ch4_ho1: R81.P$1 (1), U42.19 (HO1)
ch4_ho2: R82.P$1 (1), U42.16 (HO2)
ch4_ho3: R83.P$1 (1), U42.13 (HO3)
ch4_in: U41.2 (P0.0); also elsewhere on the board
ch4_lin1: U41.15 (P0.7), U42.1 (LIN1)
ch4_lin2: U41.13 (P1.1), U42.2 (LIN2)
ch4_lin3: U41.10 (P1.3), U42.3 (LIN3)
ch4_lo1: R84.P$1 (1), U42.11 (LO1)
ch4_lo2: R86.P$1 (1), U42.10 (LO2)
ch4_lo3: R88.P$1 (1), U42.9 (LO3)
ch4_mux1: R90.P$2 (2), R91.P$2 (2), R92.P$2 (2), U41.19 (P0.3)
ch4_mux2: R93.P$2 (2), R94.P$2 (2), R95.P$2 (2), U41.18 (P0.4)
ch4_mux3: R96.P$2 (2), R97.P$2 (2), R98.P$2 (2), U41.17 (P0.5)
ch4_vb1: C43.P$1 (1), D43.K, U42.20 (VB1)
ch4_vb2: C44.P$1 (1), D44.K, U42.17 (VB2)
ch4_vb3: C45.P$1 (1), D45.K, U42.14 (VB3)

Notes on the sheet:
Bu direnclere anlam veremedim
5-20V ile beslenebiliyor
